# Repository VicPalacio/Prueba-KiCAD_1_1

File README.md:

# Proyecto de prueba en KiCAD
aquí el problema era un tema de conexión y
## se resolvió editando el origen en kraken

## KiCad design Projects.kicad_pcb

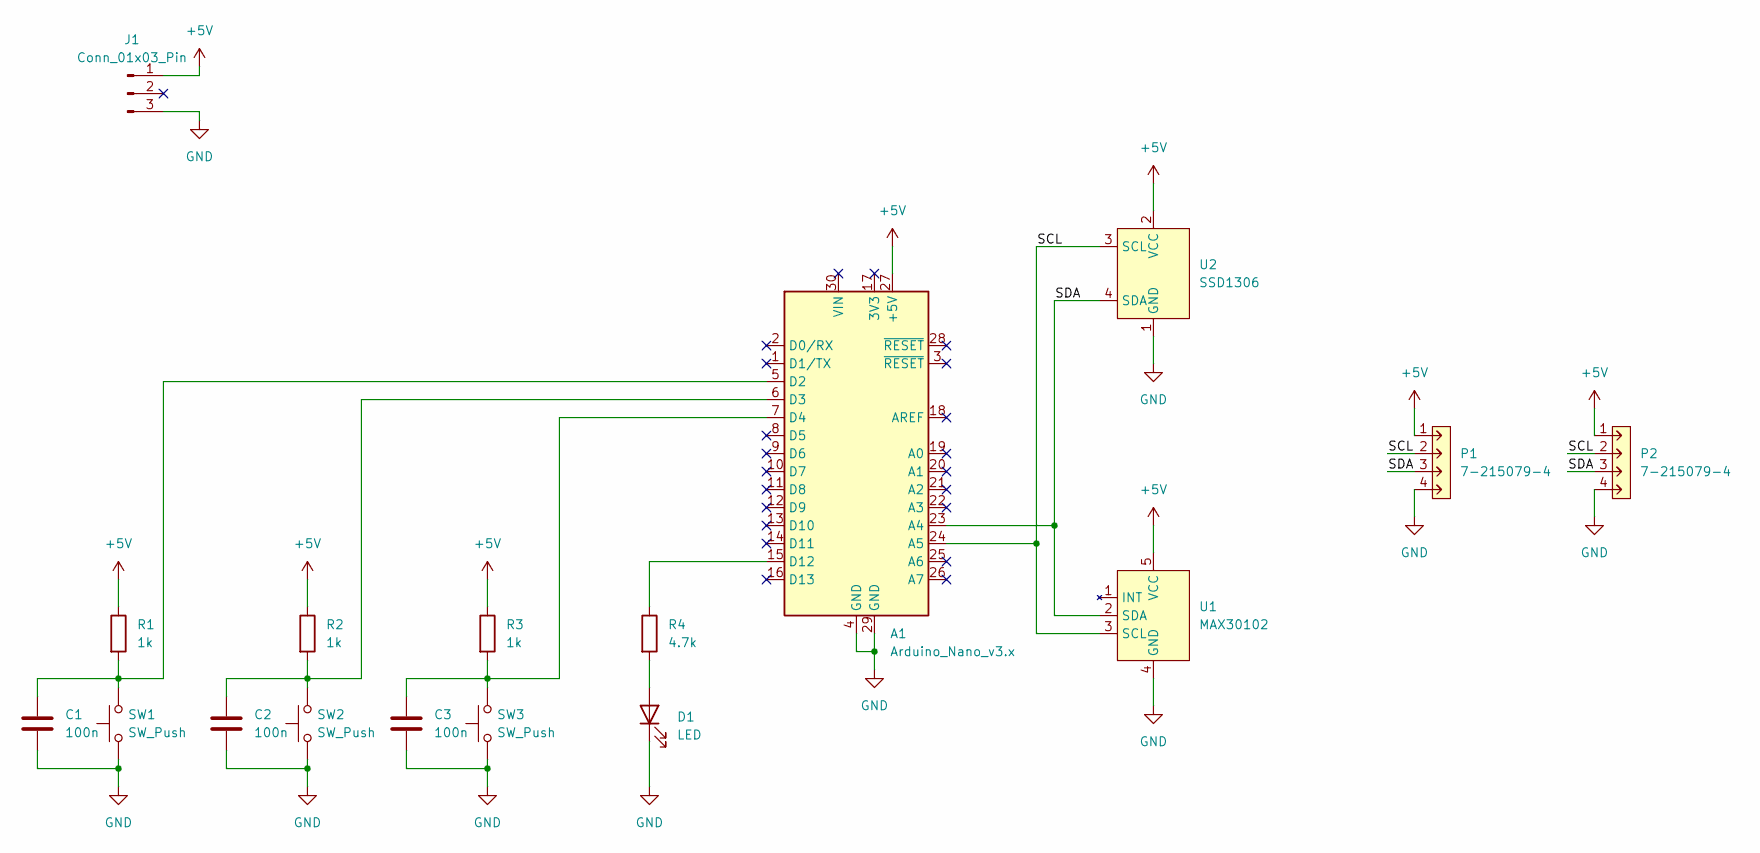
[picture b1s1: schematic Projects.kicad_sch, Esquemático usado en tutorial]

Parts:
A1: Arduino_Nano_v3.x; Arduino_Nano
C1: 100n; C_Disc_D4.7mm_W2.5mm_P5.00mm
C2, C3: 100n; C_Disc_D10.0mm_W2.5mm_P5.00mm
D1: LED; LED_D3.0mm
J1: Conn_01x03_Pin; JST_EH_B3B-EH-A_1x03_P2.50mm_Vertical
P1, P2: 7-215079-4; TE_Micro-MaTch_215079-4_2x02_P1.27mm_Vertical
R1, R2, R3: 1k; R_Axial_DIN0204_L3.6mm_D1.6mm_P5.08mm_Horizontal
R4: 4.7k; R_Axial_DIN0204_L3.6mm_D1.6mm_P5.08mm_Horizontal
SW1, SW2, SW3: SW_Push; SW_PUSH_6mm
U1: MAX30102; MAX30102_Module
U2: SSD1306

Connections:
+5V: A1.27 (+5V), J1.1, P1.1, P2.1, R1.1, R2.1, R3.1, U1.5 (VCC), U2.2 (VCC)
/SCL: A1.24 (A5), P1.2, P2.2, U1.3 (SCL), U2.3 (SCL)
/SDA: A1.23 (A4), P1.3, P2.3, U1.2 (SDA), U2.4 (SDA)
GND: A1.4 (GND), A1.29 (GND), C1.2, C2.2, C3.2, D1.1 (K), J1.3, P1.4, P2.4, SW1.1, SW2.1, SW3.1, U1.4 (GND), U2.1 (GND)
unnamed: A1.5 (D2), C1.1, R1.2, SW1.2
unnamed: A1.6 (D3), C2.1, R2.2, SW2.2
unnamed: A1.7 (D4), C3.1, R3.2, SW3.2
unnamed: A1.15 (D12), R4.1
unnamed: D1.2 (A), R4.2

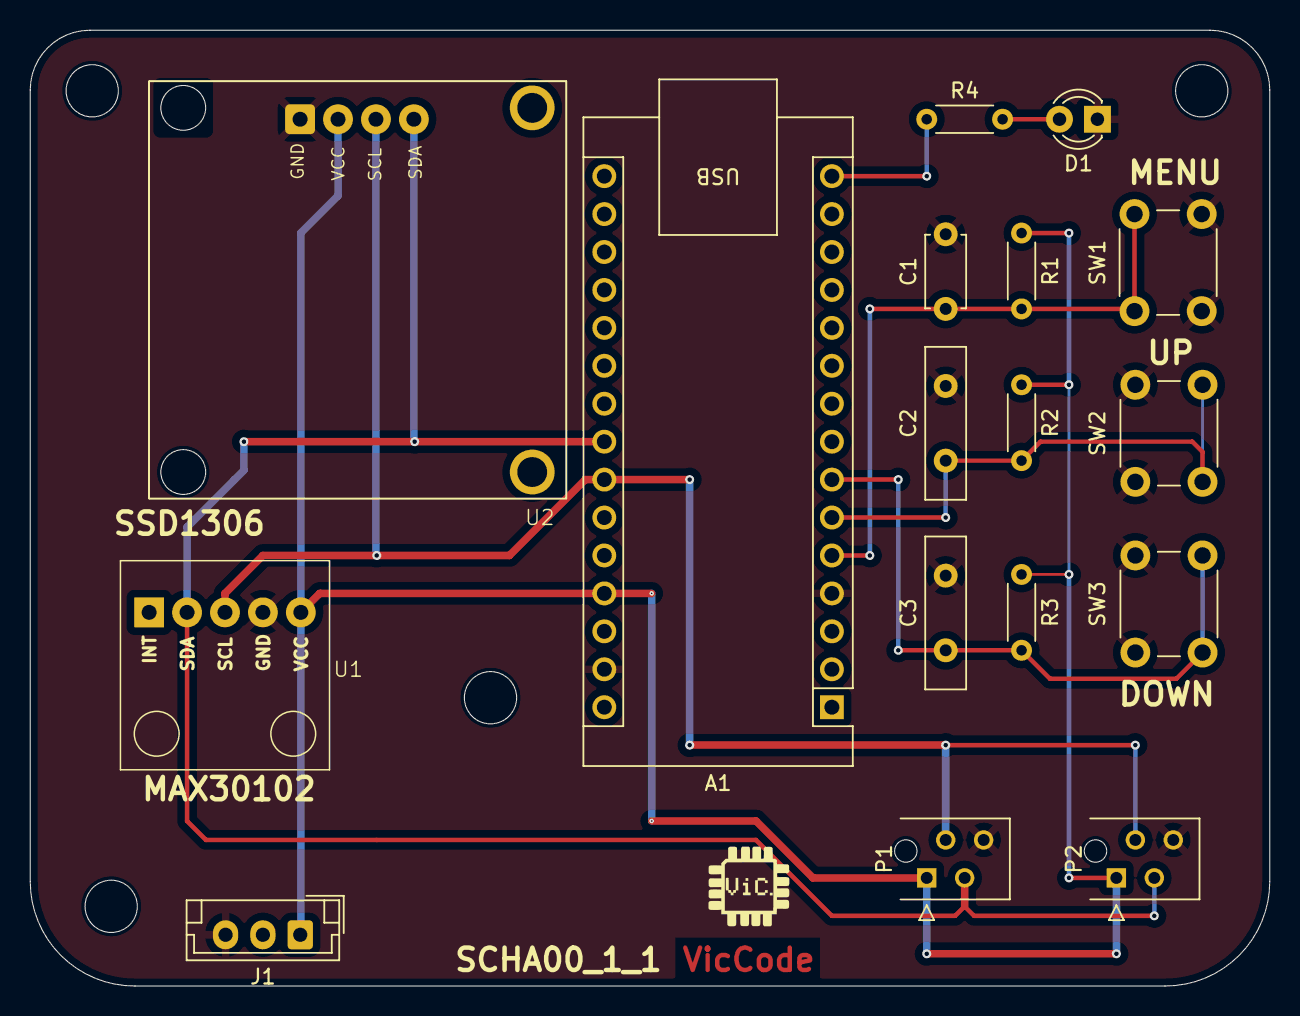
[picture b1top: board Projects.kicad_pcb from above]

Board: 2 copper layers, 83.0 x 64.0 mm, 17 parts (0 on the bottom side), 9 nets.

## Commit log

2025-07-06 Caracteristica: Primer commit del proyecto de prueba de KiCAD
2025-07-06 feat: Se agrega conector JST 1X3
    Se agrega conector para la alimentación del circuito
2025-07-09 feat: Se agrega el archivo .gitignore mas cambios en sch y pcb
    Se agregan los archivos mencionados en el titulo
2025-07-11 feat: Se termina de rutear el pcb
    Se termina de rutear el pcb
2025-07-12 feat: Generacion de archivos gerber
    Se termina el diseño del entrenamiento y se generan los archivos gerber
